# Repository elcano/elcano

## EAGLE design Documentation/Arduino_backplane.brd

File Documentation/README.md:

Elcano Project Documentation
============================

This directory contains all documentation for the Elcnao Project.

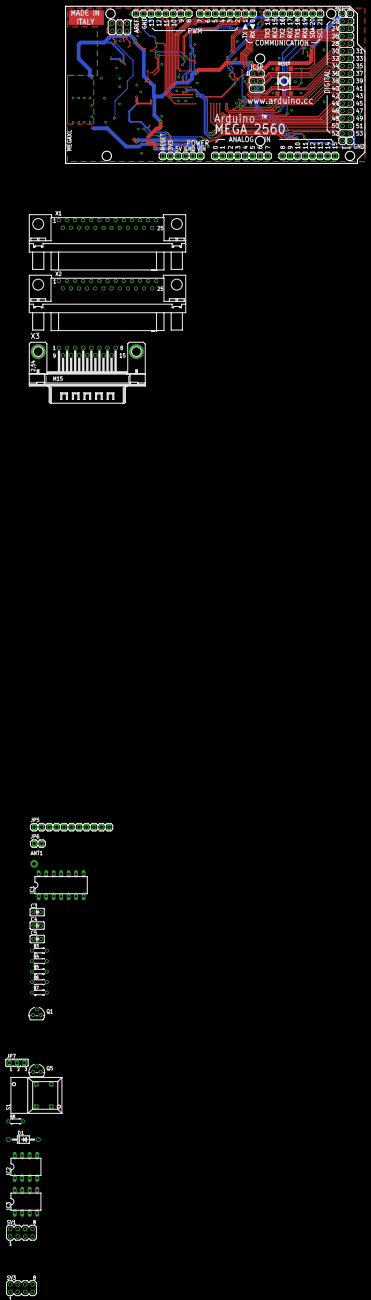
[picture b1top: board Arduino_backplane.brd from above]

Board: 2 copper layers, 101.6 x 53.3 mm, 40 parts (0 on the bottom side), 63 nets.

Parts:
ADCH: 1X08
ADCL: 1X08
ANT1: PAD-01
C3, C5: 0.1uF; C025-025X050
C4: 0.1 uF; C025-025X050
COMMUNICATION: 1X08
D1: 1N4004; DO41-10
IC1: 4013N; DIL14
IC2, IC3: MCP4802; DIL08
ICSP, ICSP1: ICSP; 2X03
JP1, JP2, JP3, JP4: 1X01
JP5: 1X11
JP6: 1X02
JP7: JP2
POWER: 1X06
PWMH: 1X08
PWML: 1X08
Q1, Q5: BF199; TO92
R3, R7: 4.7k; 0204/5
R4: 1M; 0204/5
R5, R6, R8: 10M; 0204/5
RESET: TS42
S1: 5501
SV1: MA04-2
SV3: Steer; MA04-2
X1, X2: M25-HD-20
X3: M15HP
XIOH: 2X08
XIOL: 2X08

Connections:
+5V: C5.1, IC2.1, ICSP.2, ICSP1.2, JP1.1, JP2.1, JP5.3
A1: ADCL.2, SV1.4
A4: ADCL.5, SV3.2
A5: ADCL.6, SV3.4
A10: ADCH.3, X3.2
A11: ADCH.4, X3.1
A13: ADCH.6, X2.6
A14: ADCH.7, X2.7
A15: ADCH.8, X2.8
D6: PWML.7, SV3.8
GND: C3.2, D1.C, IC2.5, IC2.7, IC3.5, IC3.7, ICSP.6, ICSP1.6, JP3.1, JP4.1, JP6.2, POWER.4, POWER.5, PWMH.7, Q1.2, R4.2, RESET.1, RESET.2, S1.NO, X2.24, X3.11
INT0: PWML.3, X3.14
INT2: COMMUNICATION.4, JP5.11
INT3: COMMUNICATION.3, JP5.10
INT4: COMMUNICATION.2, X1.17
INT5: COMMUNICATION.1, X1.16
unnamed: X3.4, XIOH.13
unnamed: PWML.6, X2.16, X3.15
unnamed: IC2.8, X3.12
unnamed: IC2.3, XIOL.2
unnamed: IC2.6, X3.13
unnamed: SV1.6, X2.22
unnamed: ADCL.8, SV3.7
unnamed: C4.1, C4.2, IC1.8, IC1.9, Q5.2, R5.1
unnamed: Q5.3, X3.6
unnamed: X1.25, X3.8
unnamed: Q1.3, X2.25
unnamed: POWER.3, SV3.6, X1.22
unnamed: IC1.11, IC1.13, JP5.6, R3.2
unnamed: ANT1.1, JP6.1
unnamed: JP7.2, R7.2
unnamed: JP5.7, S1.1A, S1.1B
unnamed: IC1.1, JP5.8, JP7.1, JP7.3
unnamed: Q5.1, R3.1
unnamed: IC1.12, R5.2
unnamed: C3.1, IC1.5, R6.1
unnamed: C5.2, IC1.4, IC1.10, R4.1
unnamed: IC1.2, R6.2
unnamed: Q1.1, R7.1
unnamed: D1.A, R8.1
PA0: X1.6, XIOH.16
PA1: X1.5, X2.5, XIOH.15
PA2: X1.7, XIOH.14
PA4: X1.8, XIOH.12
PA5: X1.4, X2.4, XIOH.11
PA6: X1.9, XIOH.10
PA7: X1.3, X2.3, XIOH.9
PB0: IC2.2, XIOL.1
PB2: IC2.4, IC3.4, ICSP.4, XIOL.3
PC0: X1.15, X2.15, XIOH.1
PC1: X1.13, X2.13, XIOH.2
PC2: X1.14, X2.14, XIOH.3
PC3: X1.12, XIOH.4
PC4: X1.1, X2.1, XIOH.5
PC5: X1.11, XIOH.6
PC6: X1.2, X2.2, XIOH.7
PC7: X1.10, XIOH.8
PD7: X1.23, XIOL.16
PL0: IC3.2, XIOL.5
PL3: X1.18, XIOL.8
PL4: SV3.5, XIOL.9
RESET: ICSP.5, POWER.1, RESET.3, RESET.4
RXD3: COMMUNICATION.7, X2.17

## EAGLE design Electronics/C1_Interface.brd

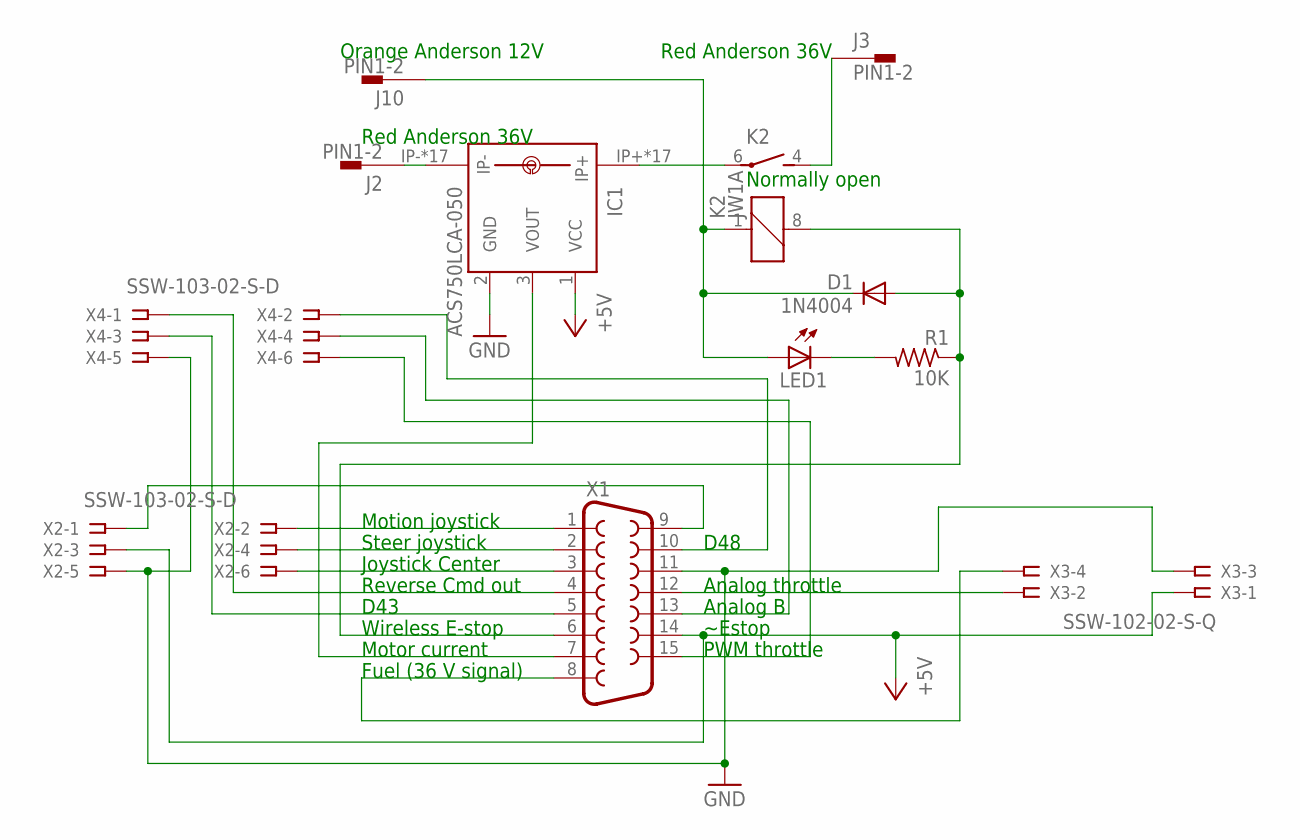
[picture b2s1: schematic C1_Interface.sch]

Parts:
D1: 1N4004; DO41-10
IC1: ACS750LCA-050; ACS75050
J2, J3, J10: PIN1-2; 62221
K2: JW1A
LED1: LED3MM
R1: 10K; 0204/5
X1: F15H
X2, X4: SSW-103-02-S-D
X3: SSW-102-02-S-Q

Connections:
+5V: IC1.1 (VCC), X1.14, X2.3, X3.1
GND: IC1.2 (GND), X1.11, X2.5, X3.3, X4.5
unnamed: D1.C, J10.1, K2.1, LED1.A
unnamed: X1.4, X4.1
unnamed: IC1.3 (VOUT), X1.7
unnamed: LED1.K (C), R1.2
unnamed: X1.8, X3.4
unnamed: J3.1, K2.4 (S)
unnamed: X1.10, X4.2
unnamed: X1.5, X4.3
unnamed: X1.13, X4.4
unnamed: D1.A, K2.8 (2), R1.1, X1.6
unnamed: X1.1, X2.2
unnamed: IC1.IP-, IC1.IP-@2 (IP-), IC1.IP-@3 (IP-), IC1.IP-@4 (IP-), IC1.IP-@5 (IP-), IC1.IP-@6 (IP-), IC1.IP-@7 (IP-), IC1.IP-@8 (IP-), IC1.IP-@9 (IP-), IC1.IP-@10 (IP-), IC1.IP-@11 (IP-), IC1.IP-@12 (IP-), IC1.IP-@13 (IP-), IC1.IP-@14 (IP-), IC1.IP-@15 (IP-), IC1.IP-@16 (IP-), IC1.IP-@17 (IP-), J2.1
unnamed: X1.2, X2.4
unnamed: X1.3, X2.6
unnamed: X1.9, X2.1
unnamed: X1.12, X3.2
unnamed: X1.15, X4.6
unnamed: IC1.IP+, IC1.IP+@2 (IP+), IC1.IP+@3 (IP+), IC1.IP+@4 (IP+), IC1.IP+@5 (IP+), IC1.IP+@6 (IP+), IC1.IP+@7 (IP+), IC1.IP+@8 (IP+), IC1.IP+@9 (IP+), IC1.IP+@10 (IP+), IC1.IP+@11 (IP+), IC1.IP+@12 (IP+), IC1.IP+@13 (IP+), IC1.IP+@14 (IP+), IC1.IP+@15 (IP+), IC1.IP+@16 (IP+), IC1.IP+@17 (IP+), K2.6

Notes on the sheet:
Motion joystick
Steer joystick
Joystick Center
Reverse Cmd out
D43
Wireless E-stop
Motor current
Fuel (36 V signal)
D48
Analog throttle
Analog B
~Estop
PWM throttle
Red Anderson 36V
Normally open
Orange Anderson 12V

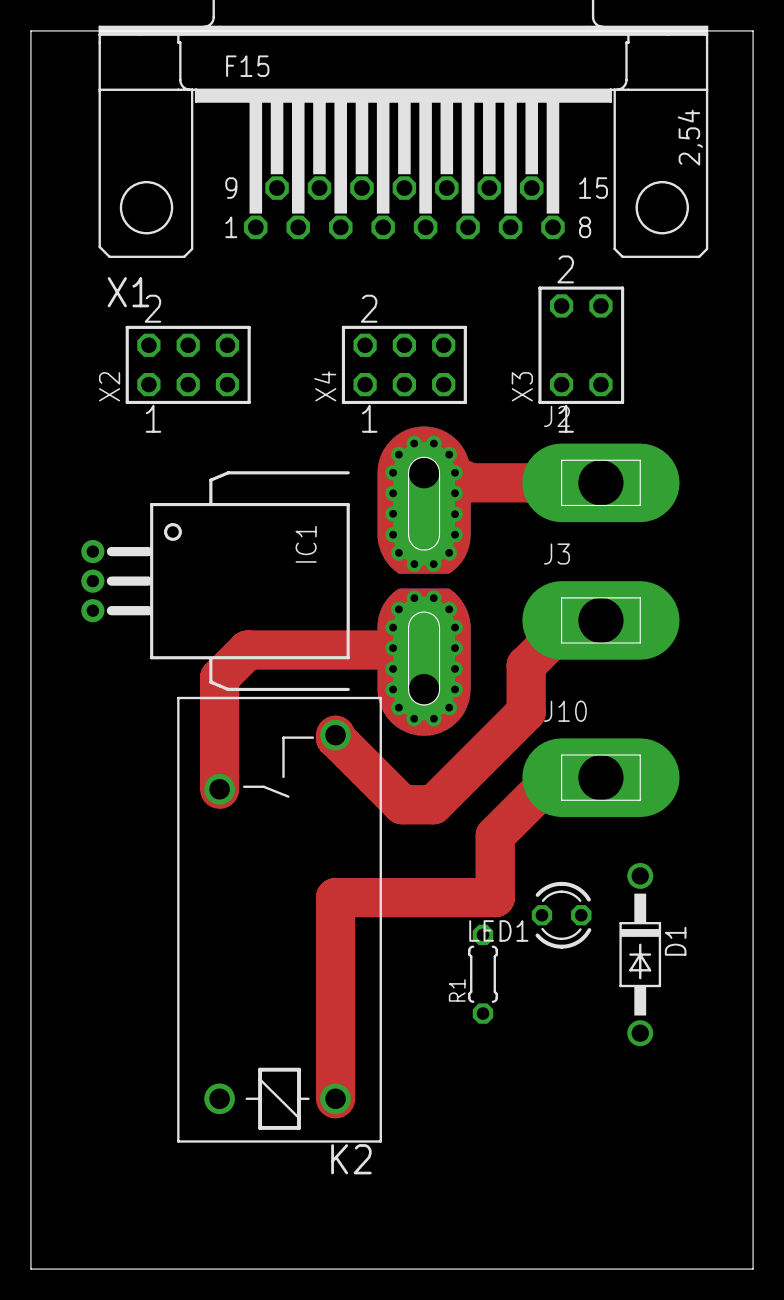
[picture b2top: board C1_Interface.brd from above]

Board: 2 copper layers, 46.7 x 80.0 mm, 12 parts (0 on the bottom side), 20 nets.

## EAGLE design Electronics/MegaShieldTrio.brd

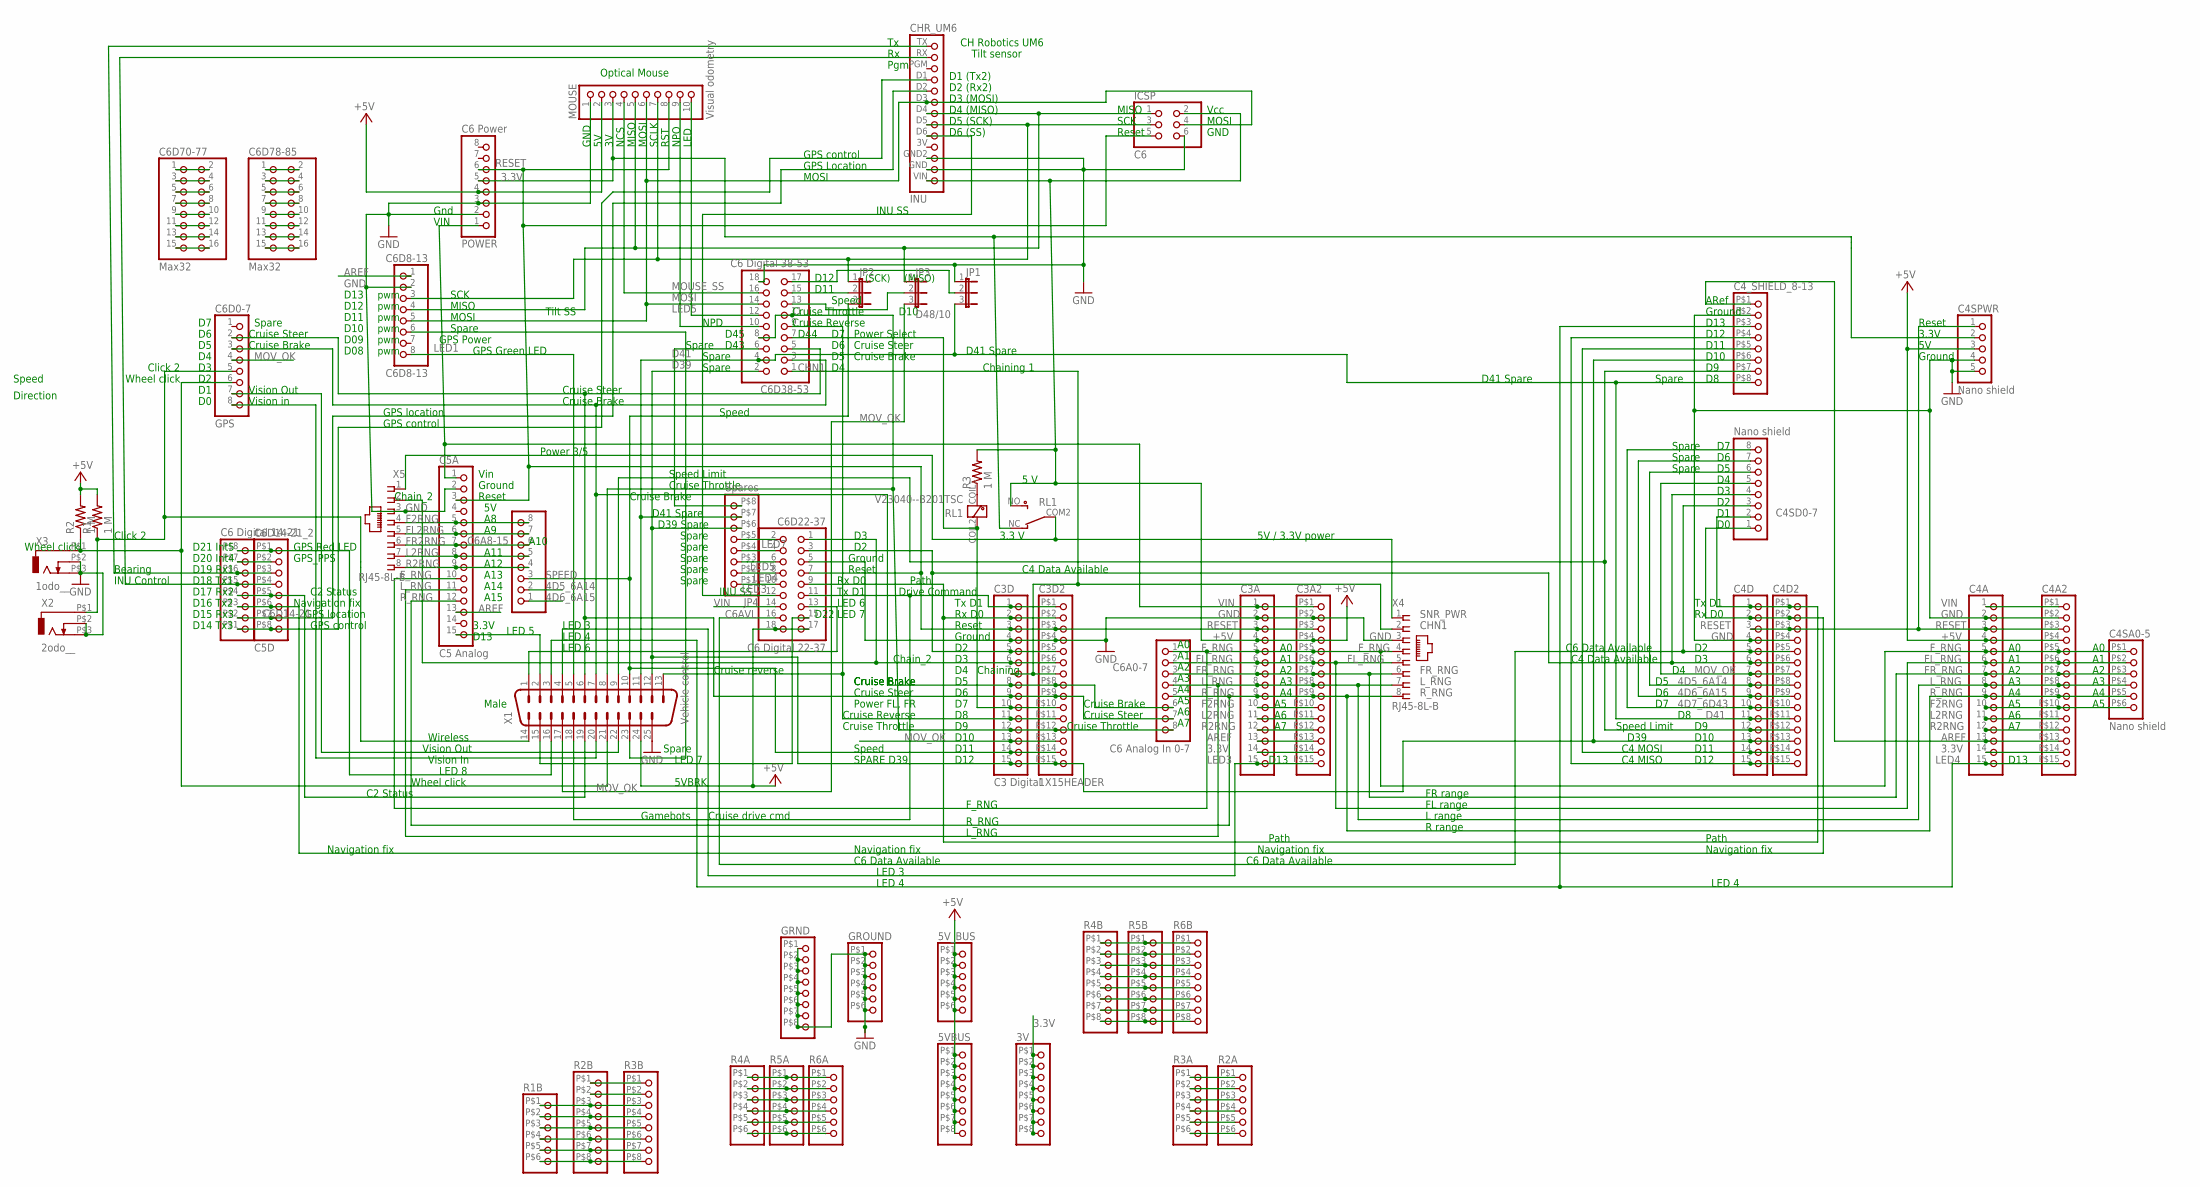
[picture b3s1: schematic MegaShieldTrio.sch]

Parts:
3V: 1X8HEADER
5VBUS: PINHD-1X8SMALL8; 1X8HEADER
5V_BUS: 1X6HEADER
C3A, C4A, C4D: 1X15
C3A2, C4A2, C4D2: 1X15HEADER
C3D: C3 Digital; 1X15
C3D2: 1X15HEADER
C4SA0-5: Nano shield; 1X6HEADER
C4SD0-7: Nano shield; 1X08
C4SPWR: Nano shield; 1X05
C4_SHIELD_8-13: 1X8HEADER
C5A: C5 Analog; 1X15
C6A0-7: C6 Analog In 0-7; 1X08
C6A8-15: 1X08
C6D0-7: GPS; 1X08
C6D8-13: C6D8-13; 1X08
C6D14-21: C6 Digital 14-21; 1X8HEADER
C6D14-21_2: C5D; 1X8HEADER
C6D22-37: C6 Digital 22-37; 2X09
C6D38-53: C6 Digital 38-53; 2X09
C6D70-77, C6D78-85: Max32; 2X08
GRND: PINHD-1X8SMALL8; 1X8HEADER
GROUND: 1X6HEADER
ICSP: C6; 2X03
INU: CHR_UM6
JP1, JP2: JP2
JP3: D48/10; JP2
JP4: Spares; 1X8HEADER
MOUSE: Visual odometry; 1X10
POWER: C6 Power; 1X08
R1, R2, R3: 1 M; 0207/10
R1B, R2A, R3A, R4A, R5A: 1X6HEADER
R2B, R3B, R4B, R5B, R6B: PINHD-1X8SMALL8; 1X8HEADER
R6A: 1X6HEADER
RL1: V23040--B201TSC; TSC-112L3H
X1: Vehicle control; M25H
X2: 2odo__; ODO_JACK
X3: 1odo__; ODO_JACK
X4, X5: RJ45-8L-B; RJ45-NO-SHIELD

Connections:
3.3V: 3V.P$1 (1), 3V.P$2 (2), 3V.P$3 (3), 3V.P$4 (4), 3V.P$5 (5), 3V.P$6 (6), 3V.P$7 (7), 3V.P$8 (8), C3A.14, C3A2.P$14 (14), C4A.14, C4A2.P$14 (14), C4SPWR.2, MOUSE.3, POWER.5, RL1.NC (4)
4D5_6A14: C4D.8, C4D2.P$8 (8), C4SD0-7.6, C6A8-15.2
4D6_6A15: C4D.9, C4D2.P$9 (9), C4SD0-7.7, C6A8-15.1
4D7_6D43: C4D.10, C4D2.P$10 (10), C4SD0-7.8
6D10_2A6: C6D8-13.6, X1.23
+5V: 5VBUS.P$1 (1), 5VBUS.P$2 (2), 5VBUS.P$3 (3), 5VBUS.P$4 (4), 5VBUS.P$5 (5), 5VBUS.P$6 (6), 5VBUS.P$7 (7), 5VBUS.P$8 (8), 5V_BUS.P$1 (1), 5V_BUS.P$2 (2), 5V_BUS.P$3 (3), 5V_BUS.P$4 (4), 5V_BUS.P$5 (5), 5V_BUS.P$6 (6), C3A.4, C3A2.P$4 (4), C4A.4, C4A2.P$4 (4), C4SPWR.3, C6D22-37.17, C6D22-37.18, ICSP.2, INU.VIN (1), MOUSE.2, POWER.4, R1.2, R2.2, R3.2, RL1.NO (6), X1.24
AREF: C3A.13, C3A2.P$13 (13), C4A.13, C4A2.P$13 (13), C4_SHIELD_8-13.P$1 (1), C5A.13, C6D8-13.1
C2STAT: C6D14-21.P$4 (4), C6D14-21_2.P$5 (5), X1.19
C4AVL: C3D.5, C3D2.P$5 (5), C4D.6, C4D2.P$6 (6), C4SD0-7.4, C6D22-37.3
C4D11: C4D.14, C4D2.P$14 (14), C4_SHIELD_8-13.P$5 (5)
C4D12: C4D.15, C4D2.P$15 (15), C4_SHIELD_8-13.P$4 (4)
C6AVL: C4D.5, C4D2.P$5 (5), C4SD0-7.3, C6D22-37.16
C6D29: C6D22-37.10, JP4.P$1 (1)
C6D31: C6D22-37.8, JP4.P$2 (2)
C6D33: C6D22-37.6, JP4.P$3 (3)
C6D35: C6D22-37.4, JP4.P$4 (4)
C6D37: C6D22-37.2, JP4.P$5 (5)
CHN1: C3D.7, C3D2.P$7 (7), C6D38-53.1, X4.2
CHN2: C3D.6, C3D2.P$6 (6), C6D22-37.1, X5.2
CLICK1: C6D0-7.6, R2.1, X1.21, X3.P$1 (1)
CLICK2: C6D0-7.5, R1.1, X1.14, X2.P$1 (1)
CRS_BRK: C3D.8, C3D2.P$8 (8), C6A0-7.6, C6D0-7.3, C6D38-53.3, X1.7
CRS_REV: C3D.11, C3D2.P$11 (11), C6D38-53.9, X1.13
CRS_STR: C3D.9, C3D2.P$9 (9), C6A0-7.7, C6D0-7.2, C6D38-53.5, X1.6
CRS_THR: C3D.12, C3D2.P$12 (12), C6A0-7.8, C6D38-53.8, C6D38-53.11, X1.8
D39: C3D.15, C3D2.P$15 (15), C4D.13, C4D2.P$13 (13), C4_SHIELD_8-13.P$6 (6), C6D38-53.2, JP4.P$6 (6), X1.12
D41: C4D.11, C4D2.P$11 (11), C4_SHIELD_8-13.P$8 (8), C6D38-53.4, JP1.3, JP4.P$7 (7), X1.11
DRV_CMD: C3D.1, C3D2.P$1 (1), C6D22-37.11, X1.18
F2RNG: C3A.10, C3A2.P$10 (10), C4A.10, C4A2.P$10 (10), C4SA0-5.P$6 (6), C5A.5, C6A8-15.8, X5.4
FL2RNG: C5A.6, C6A8-15.7, X5.5
FL_RNG: C3A.6, C3A2.P$6 (6), C4A.6, C4A2.P$6 (6), C4SA0-5.P$2 (2), C6A0-7.2, X4.5
FR2RNG: C5A.7, C6A8-15.6, X5.6
FR_RNG: C3A.7, C3A2.P$7 (7), C4A.7, C4A2.P$7 (7), C4SA0-5.P$3 (3), C6A0-7.3, X4.6
F_RNG: C3A.5, C3A2.P$5 (5), C4A.5, C4A2.P$5 (5), C4SA0-5.P$1 (1), C5A.10, C6A0-7.1, X4.4
GND: C3A.2, C3A2.P$2 (2), C3D.4, C3D2.P$4 (4), C4A.2, C4A2.P$2 (2), C4D.4, C4D2.P$4 (4), C4SPWR.4, C4SPWR.5, C4_SHIELD_8-13.P$2 (2), C5A.2, C6D8-13.2, C6D22-37.5, C6D38-53.18, GRND.P$1 (1), GRND.P$2 (2), GRND.P$3 (3), GRND.P$4 (4), GRND.P$5 (5), GRND.P$6 (6), GRND.P$7 (7), GRND.P$8 (8), GROUND.P$1 (1), GROUND.P$2 (2), GROUND.P$3 (3), GROUND.P$4 (4), GROUND.P$5 (5), GROUND.P$6 (6), ICSP.6, INU.GND (2), INU.GND2 (3), JP1.1, MOUSE.1, POWER.2, POWER.3, X1.25, X2.P$2 (2), X2.P$3 (3), X3.P$2 (2), X3.P$3 (3), X4.3, X5.3
GPS_CNTRL: C6D14-21.P$1 (1), C6D14-21_2.P$8 (8), INU.D1 (10)
GPS_LOC: C6D14-21.P$2 (2), C6D14-21_2.P$7 (7), INU.D2 (9)
INU_BRN: C6D14-21.P$6 (6), C6D14-21_2.P$3 (3), INU.TX (13)
INU_CNTRL: C6D14-21.P$5 (5), C6D14-21_2.P$4 (4), INU.RX (12)
INU_SS: C6D22-37.12, INU.D6 (5)
L2RNG: C3A.11, C3A2.P$11 (11), C4A.11, C4A2.P$11 (11), C5A.8, C6A8-15.5, X5.7
LED1: C6D8-13.8, X1.5
LED3: C3A.15, C3A2.P$15 (15), X1.4
LED4: C4A.15, C4A2.P$15 (15), C4_SHIELD_8-13.P$3 (3), X1.3
LED5: C5A.15, C6D38-53.12, MOUSE.10, X1.2
LED6: C6D22-37.13, X1.1
LED7: C6D22-37.15, X1.15
LED8: C6D14-21.P$8 (8), C6D14-21_2.P$1 (1), X1.16
L_RNG: C3A.8, C3A2.P$8 (8), C4A.8, C4A2.P$8 (8), C4SA0-5.P$4 (4), C5A.11, C6A0-7.4, X4.7
MISO: C6D8-13.4, ICSP.1, INU.D4 (7), JP3.1, MOUSE.5
MOSI: C6D8-13.5, C6D38-53.14, ICSP.4, INU.D3 (8), MOUSE.6
MOUSE_SS: C6D38-53.16, MOUSE.4
MOV_OK: C3D.13, C3D2.P$13 (13), C4D.7, C4D2.P$7 (7), C4SD0-7.5, C6D0-7.4, JP3.3, X1.17
unnamed: R2B.P$1 (1), R3B.P$1 (1)
unnamed: R2B.P$2 (2), R3B.P$2 (2)
unnamed: C6D38-53.6, JP4.P$8 (8)
unnamed: C6D38-53.15, JP2.2
unnamed: C6D38-53.13, JP3.2
unnamed: C6D38-53.17, JP1.2
unnamed: C6D14-21.P$7 (7), C6D14-21_2.P$2 (2)
unnamed: R3.1, RL1.COIL1 (1)
unnamed: R1B.P$1 (1), R2B.P$3 (3), R3B.P$3 (3)
unnamed: R1B.P$2 (2), R2B.P$4 (4), R3B.P$4 (4)
unnamed: R1B.P$3 (3), R2B.P$5 (5), R3B.P$5 (5)
unnamed: R1B.P$4 (4), R2B.P$6 (6), R3B.P$6 (6)
unnamed: R1B.P$5 (5), R2B.P$7 (7), R3B.P$7 (7)
unnamed: R1B.P$6 (6), R2B.P$8 (8), R3B.P$8 (8)
unnamed: R4A.P$1 (1), R5A.P$1 (1), R6A.P$1 (1)
unnamed: R4A.P$2 (2), R5A.P$2 (2), R6A.P$2 (2)
unnamed: R4A.P$3 (3), R5A.P$3 (3), R6A.P$3 (3)
unnamed: R4A.P$4 (4), R5A.P$4 (4), R6A.P$4 (4)
unnamed: R4A.P$5 (5), R5A.P$5 (5), R6A.P$5 (5)
unnamed: R4A.P$6 (6), R5A.P$6 (6), R6A.P$6 (6)
unnamed: R4B.P$1 (1), R5B.P$1 (1), R6B.P$1 (1)
unnamed: C6D78-85.1, C6D78-85.2
unnamed: C6D78-85.3, C6D78-85.4
unnamed: R4B.P$2 (2), R5B.P$2 (2), R6B.P$2 (2)
unnamed: R4B.P$3 (3), R5B.P$3 (3), R6B.P$3 (3)
unnamed: C6D78-85.5, C6D78-85.6
unnamed: R4B.P$5 (5), R5B.P$5 (5), R6B.P$5 (5)
unnamed: C6D78-85.7, C6D78-85.8
unnamed: C6D78-85.9, C6D78-85.10
unnamed: R4B.P$6 (6), R5B.P$6 (6), R6B.P$6 (6)
unnamed: R4B.P$7 (7), R5B.P$7 (7), R6B.P$7 (7)
unnamed: R4B.P$8 (8), R5B.P$8 (8), R6B.P$8 (8)
unnamed: R2A.P$1 (1), R3A.P$1 (1)
unnamed: R2A.P$2 (2), R3A.P$2 (2)
unnamed: C6D78-85.11, C6D78-85.12
unnamed: C6D78-85.13, C6D78-85.14
unnamed: C6D78-85.15, C6D78-85.16
unnamed: R2A.P$3 (3), R3A.P$3 (3)
unnamed: C6D70-77.1, C6D70-77.2
unnamed: R2A.P$4 (4), R3A.P$4 (4)
unnamed: R2A.P$5 (5), R3A.P$5 (5)
unnamed: C6D70-77.3, C6D70-77.4
unnamed: C6D70-77.5, C6D70-77.6
unnamed: C6D70-77.7, C6D70-77.8
unnamed: C6D70-77.9, C6D70-77.10
unnamed: C6D70-77.11, C6D70-77.12
unnamed: C6D70-77.13, C6D70-77.14
unnamed: C6D70-77.15, C6D70-77.16
unnamed: R2A.P$6 (6), R3A.P$6 (6)
NAV_FIX: C4D.2, C4D2.P$2 (2), C4SD0-7.1, C6D14-21.P$3 (3), C6D14-21_2.P$6 (6)
NPD: C6D38-53.10, MOUSE.9
PATH: C3D.2, C3D2.P$2 (2), C4D.1, C4D2.P$1 (1), C4SD0-7.2, C6D22-37.9
PWR_SEL: C3D.10, C3D2.P$10 (10), C6D38-53.7, RL1.COIL2 (2)
R2RNG: C3A.12, C3A2.P$12 (12), C4A.12, C4A2.P$12 (12), C5A.9, C6A8-15.4, X5.8
R5B: R4B.P$4 (4), R5B.P$4 (4), R6B.P$4 (4)
RESET: C3A.3, C3A2.P$3 (3), C3D.3, C3D2.P$3 (3), C4A.3, C4A2.P$3 (3), C4D.3, C4D2.P$3 (3), C4SPWR.1, C5A.3, C6D22-37.7, ICSP.5, MOUSE.8, POWER.6
R_RNG: C3A.9, C3A2.P$9 (9), C4A.9, C4A2.P$9 (9), C4SA0-5.P$5 (5), C5A.12, C6A0-7.5, X4.8
SCK: C6D8-13.3, ICSP.3, INU.D5 (6), JP2.1, MOUSE.7
SNR_PWR: RL1.COM2 (5), X4.1, X5.1
SPD_LMT: C4D.12, C4D2.P$12 (12), C4_SHIELD_8-13.P$7 (7), X1.9
SPEED: C3D.14, C3D2.P$14 (14), C6A8-15.3, JP2.3, X1.10
VIN: C3A.1, C3A2.P$1 (1), C4A.1, C4A2.P$1 (1), C5A.1, C6D22-37.14, POWER.1
VIS_IN: C6D0-7.8, X1.20
VIS_OUT: C6D0-7.7, X1.22

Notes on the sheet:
pwm
(SCK)
(MISO)
Cruise Brake
Cruise Throttle
Cruise Steer
Gnd
Male
A10
A11
A13
A14
A15
5VBRK
D45
D43
D10
D11
D12
D13
D09
D08
VIN
Rx D0
Tx D1
Reset
Ground
3.3V
ARef
Path
Navigation fix
D14 Tx3
D15 Rx3
D16 Tx2
D17 Rx2
D18 Tx1
D19 Rx1
D20 Int4
D21 Int5
C6 Data Available

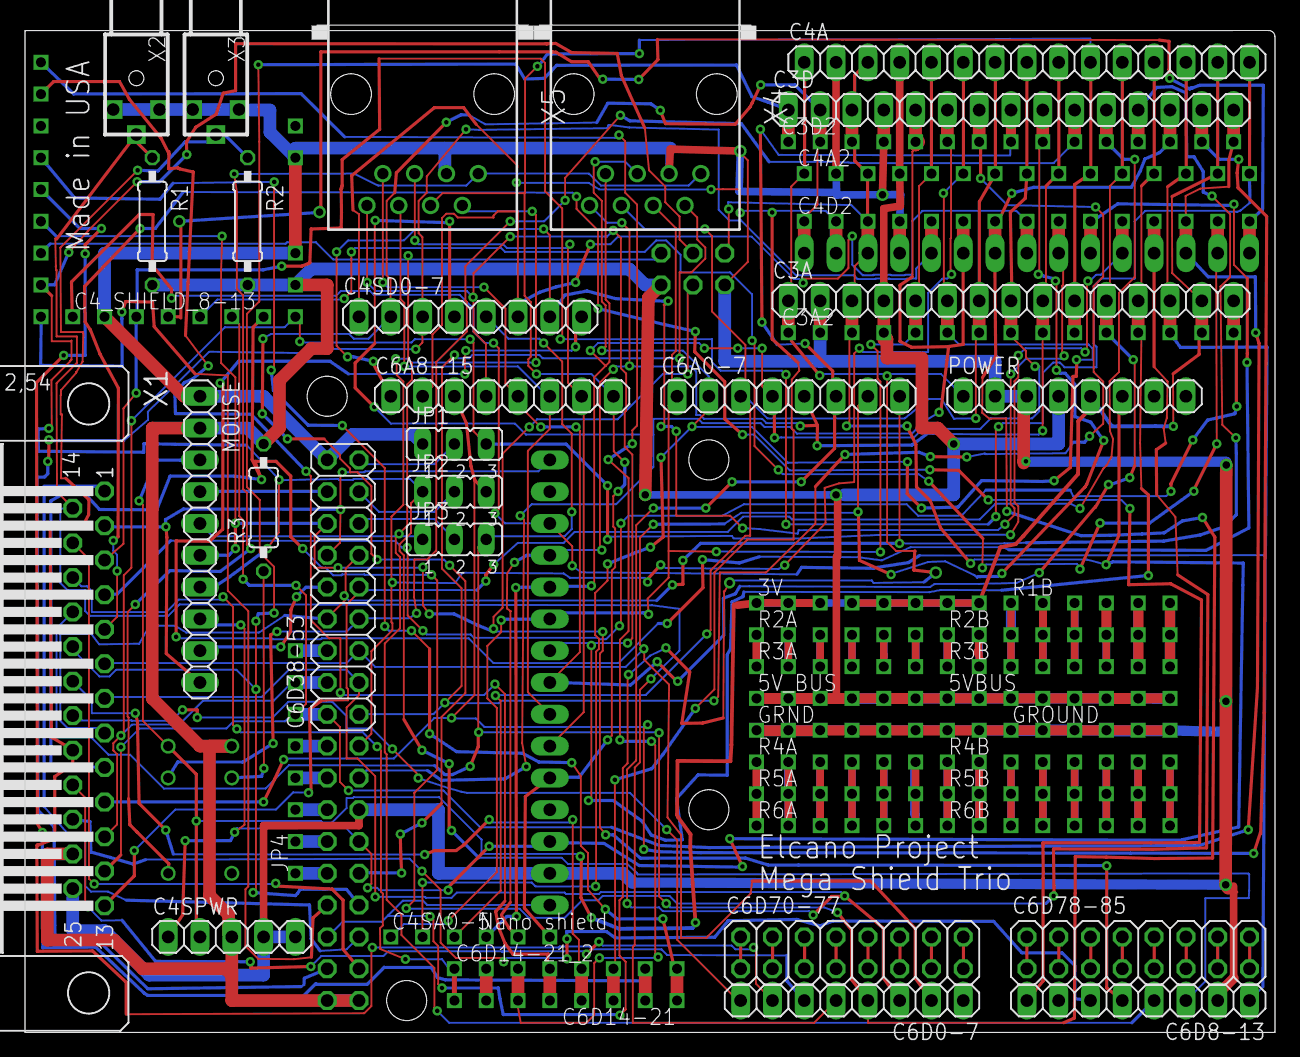
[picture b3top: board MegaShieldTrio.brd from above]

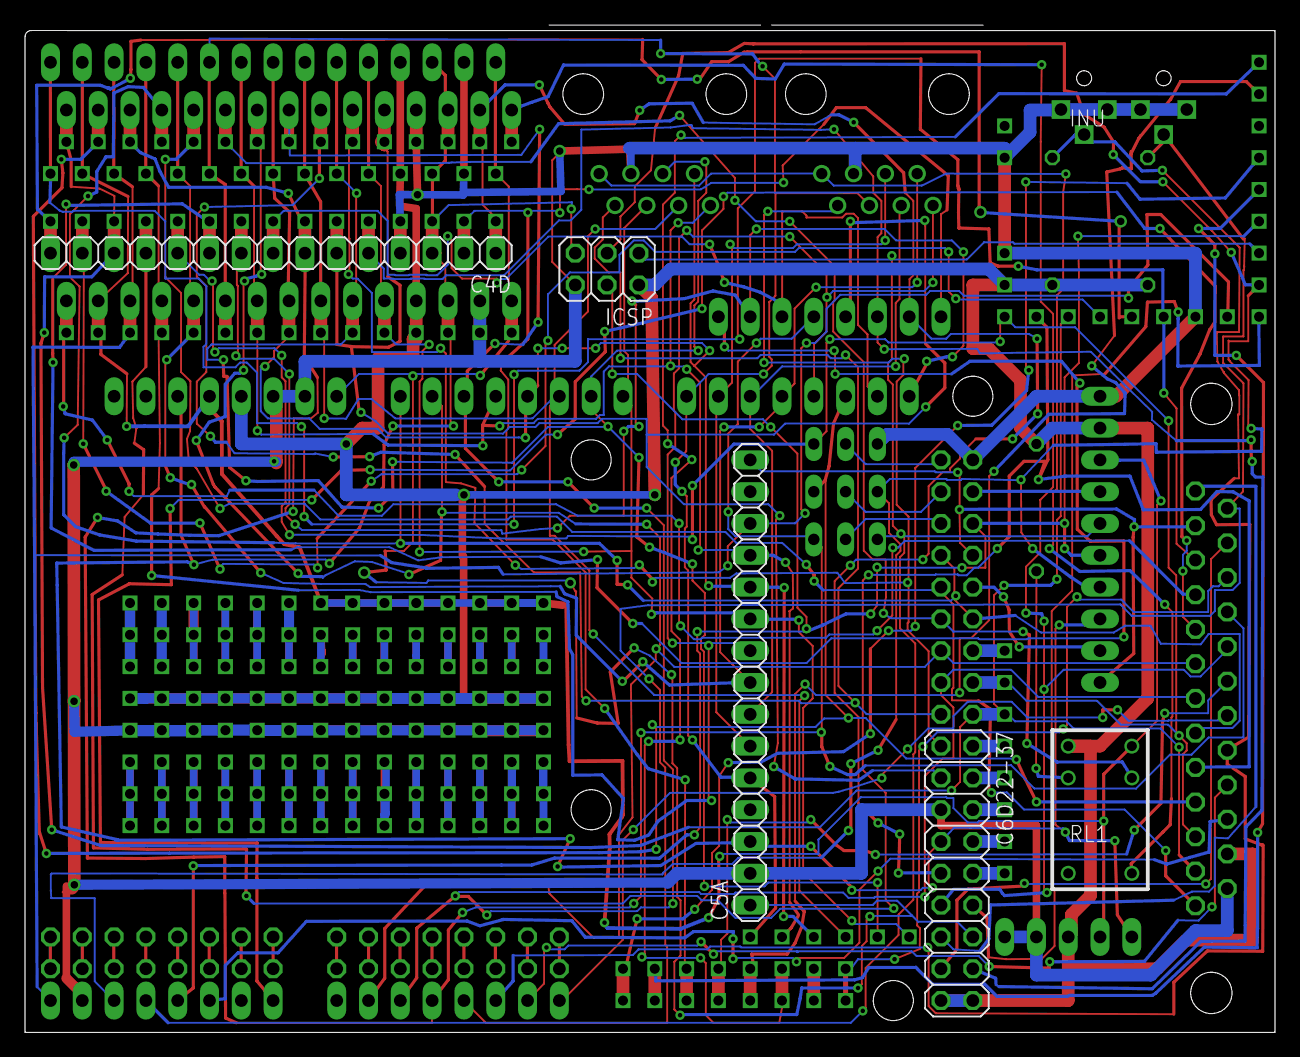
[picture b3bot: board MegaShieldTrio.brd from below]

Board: 2 copper layers, 99.8 x 80.0 mm, 56 parts (6 on the bottom side), 117 nets.

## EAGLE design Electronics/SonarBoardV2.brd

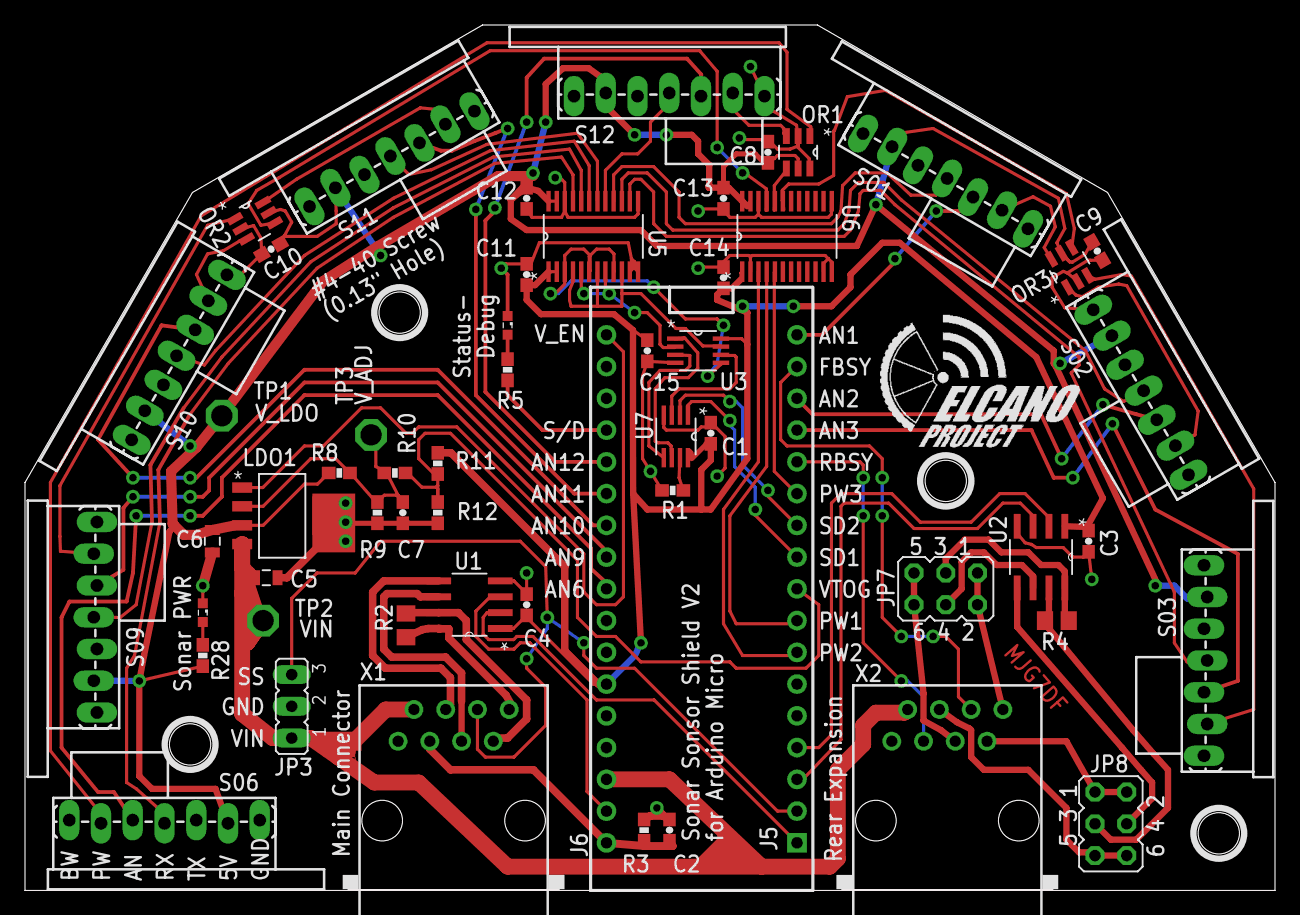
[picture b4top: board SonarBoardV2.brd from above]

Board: 2 copper layers, 100.0 x 69.2 mm, 60 parts (0 on the bottom side), 69 nets.

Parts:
C1, C3, C4, C8, C9, C10, C11, C12, C13, C14, C15: 0.1uF; 0603-CAP
C2, C7: DNS; 0603-CAP
C5, C6: 10uF, 25V; 0805
J5: HEAD17-NOSS
J6: HEAD17-NOSS-1
JP3: JP2
JP7, JP8: JP3Q
LDO1: LP38693MP-ADJ; SOT150P696X180-5N
LED1, LED2: SML0603
OR1, OR2, OR3: SN74LVC1G332DBVR; SOT95P280X145-6N
R1: 0; 0603-RES
R2, R4: 100; R0805
R3, R11, R12: DNS; 0603-RES
R5, R28: 600; 0603-RES
R8: 33k; 0603-RES
R9: 12k; 0603-RES
R10: 100k; 0603-RES
S01, S02, S03, S06, S09, S10, S11, S12: MaxSonar; XL-MAXSONAR-PACKAGE
TP1, TP2, TP3: TPPAD1-17; P1-17
U1, U2: DS8921M; SOIC127O620X175-8N
U3: SN74LVC3G14DCTR; SOP65P400X130-8N
U5, U6: SN74LVCH8T245PWR; SOP65P640X120-24N
U7: SN74LVC1G139DCTR; SOP65P400X130-8N@1
U$15, U$16, U$17, U$18: STAND-OFF
X1, X2: RJ45-8L-B; RJ45-NO-SHIELD

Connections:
+5V: C1.1, C3.1, C4.1, C11.1, C14.1, C15.1, J6.6, R11.2, U1.1, U2.1, U3.8, U5.1, U5.2, U6.1, U7.8
A0: J6.14, R5.1
AN1: J5.17, S01.3
AN2: J5.15, S02.3
AN3: J5.14, S03.3
AN6: J6.9, S06.3
AN9: J6.10, S09.3
AN10: J6.11, S10.3
AN11: J6.12, S11.3
AN12: J6.13, S12.3
F_BSY: J5.16, X2.6
G01: U3.7, U5.4, U5.7, U5.10
G10: U3.5, U5.3, U5.6, U5.9
G11: U3.2, U5.5, U5.8
GND: C1.2, C2.2, C3.2, C4.2, C5.2, C6.2, C7.2, C8.2, C9.2, C10.2, C11.2, C12.2, C13.2, C14.2, C15.2, J5.6, J6.4, JP3.2, LDO1.5, LED1.C, LED2.C, OR1.2, OR1.6, OR2.2, OR3.2, R1.2, R3.1, R9.1, R12.1, S01.1, S01.7, S02.1, S02.7, S03.1, S03.7, S06.1, S06.7, S09.1, S09.7, S10.1, S10.7, S11.1, S11.7, S12.1, S12.7, U1.4, U2.4, U3.4, U5.11, U5.12, U5.13, U5.22, U6.2, U6.11, U6.12, U6.13, U6.22, U7.4, X1.1, X2.1
MISO: J6.2, U1.3
MISO+: U1.6, X1.5
MISO-: U1.5, X1.4
MOSI: J5.1, U1.2
MOSI+: R2.1, U1.8, X1.8
MOSI-: R2.2, U1.7, X1.7
MRX+_STX+: JP7.1, JP7.2, X2.8
MRX-_STX-: JP8.1, JP8.2, X2.7
MTX+_SRX+: JP7.5, JP7.6, X2.5
MTX-_SRX-: JP8.5, JP8.6, X2.4
unnamed: LED2.A, R5.2
unnamed: LED1.A, R28.2
unnamed: U3.1, U7.6
unnamed: U3.3, U7.5
unnamed: U3.6, U7.3
unnamed: R1.1, U7.7
unnamed: OR1.4, U6.20
unnamed: OR2.4, U6.21
unnamed: OR3.4, U6.19
PW1: OR3.6, S01.2
PW2: OR3.1, S02.2
PW3: OR3.3, S03.2
PW6: OR1.1, S06.2
PW9: OR2.1, S09.2
PW10: OR2.3, S10.2
PW11: OR2.6, S11.2
PW12: OR1.3, S12.2
PW_OR1: J5.8, U6.4
PW_OR2: J5.7, U6.3
PW_OR3: J5.12, U6.5
RX: J5.4, U2.2
RX1: S01.4, U5.16
RX2: S02.4, U5.15
RX3: S03.4, U5.14
RX6: S06.4, U5.21
RX9: S09.4, U5.20
RX10: S10.4, U5.19
RX11: S11.4, U5.18
RX12: S12.4, U5.17
RX+: JP7.3, R4.1, U2.8
RX-: JP8.3, R4.2, U2.7
R_BSY: J5.13, X2.3
SCK: C2.1, J6.1, R3.2, X1.3
SS: J5.2, JP3.3, X1.6
S_DEC_1: J5.10, U7.1
S_DEC_2: J5.11, U7.2
TX: J5.3, U2.3
TX+: JP7.4, U2.6
TX-: JP8.4, U2.5
VIN: C5.1, J6.3, JP3.1, LDO1.4, TP2.TP, X1.2, X2.2
V_ADJ: C7.1, LDO1.2, R8.1, R9.2, R10.2, TP3.TP
V_EN: J6.17, LDO1.1
V_LDO: C6.1, C8.1, C9.1, C10.1, C12.1, C13.1, LDO1.3, OR1.5, OR2.5, OR3.5, R8.2, R28.1, S01.6, S02.6, S03.6, S06.6, S09.6, S10.6, S11.6, S12.6, TP1.TP, U5.23, U5.24, U6.23, U6.24
V_TOGGLE: J5.9, R10.1, R11.1, R12.2

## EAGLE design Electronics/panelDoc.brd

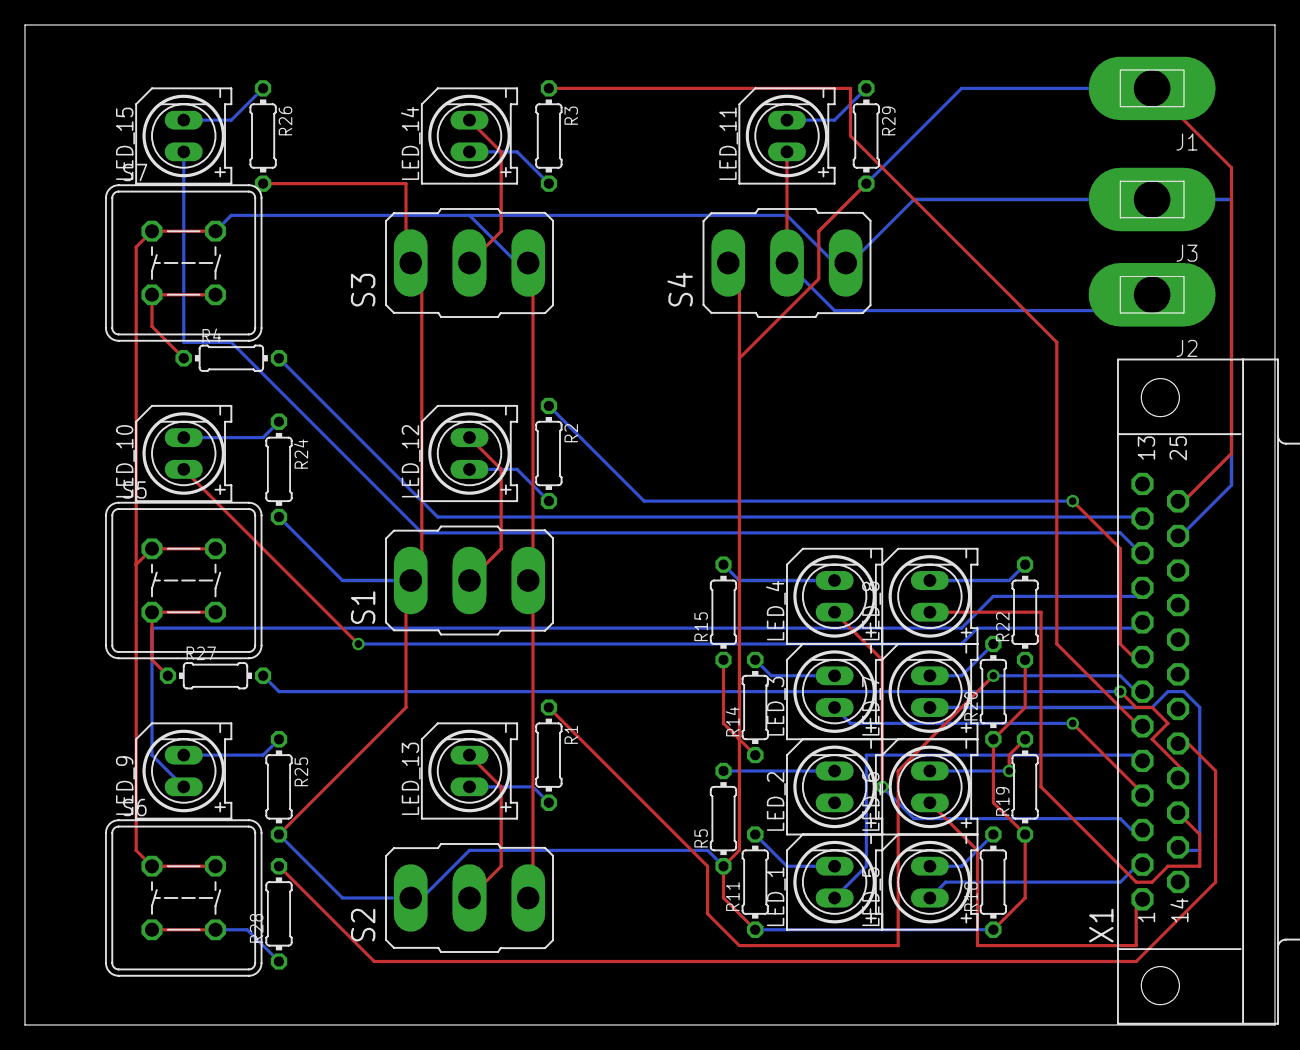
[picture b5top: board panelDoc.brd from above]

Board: 2 copper layers, 100.0 x 80.0 mm, 44 parts (0 on the bottom side), 40 nets.

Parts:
J1, J2, J3: PIN1-2; 62221
LED_1, LED_2, LED_3, LED_4, LED_5, LED_6, LED_7, LED_8: Q62902-B156
LED_9: Stop LED; Q62902-B156
LED_10: Cruise LED; Q62902-B156
LED_11: On LED; Q62902-B156
LED_12: Motor LED; Q62902-B156
LED_13: Brake LED; Q62902-B156
LED_14: Steer LED; Q62902-B156
LED_15: Reverse LED; Q62902-B156
R1, R2, R3: 200; 0204/7
R4, R27, R28: 220; 0204/7
R5, R11, R14, R15, R18, R19, R20, R22, R24, R25, R26: 1K; 0204/7
R29: 10K; 0204/7
S1: Motor; M9040P
S2: Brake; M9040P
S3: Steer; M9040P
S4: On; M9040P
S5: Cruise Switch; DTE6K
S6: Stop switch; DTE6K
S7: Reverse Switch; DTE6K
X1: 182-025-MALE

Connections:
+5V: J3.1, S1.3, S2.3, S3.3, S4.3, S5.1, S5.2, S6.1, S6.2, S7.1, S7.2, X1.24
GND: J1.1, R5.1, R11.1, R14.1, R15.1, R18.1, R19.1, R20.1, R22.1, R24.2, R25.2, R26.2, R29.2, S1.1, S2.1, S3.1, S4.1, X1.25
unnamed: R3.1, X1.6
unnamed: LED_8.K, R22.2
unnamed: LED_10.K, R24.1
unnamed: LED_3.K, R14.2
unnamed: LED_3.A, X1.4
unnamed: LED_4.K, R15.2
unnamed: LED_4.A, X1.3
unnamed: LED_1.A, X1.5
unnamed: LED_8.A, X1.16
unnamed: LED_5.K, R18.2
unnamed: LED_5.A, X1.2
unnamed: LED_6.K, R19.2
unnamed: LED_6.A, X1.1
unnamed: LED_7.K, R20.2
unnamed: LED_10.A, X1.9
unnamed: LED_1.K, R11.2
unnamed: J2.1, LED_11.A, S4.2
unnamed: LED_11.K, R29.1
unnamed: R27.2, X1.17
unnamed: LED_7.A, X1.15
unnamed: LED_12.A, R2.2
unnamed: LED_15.A, X1.11
unnamed: LED_12.K, S1.2
unnamed: LED_13.K, S2.2
unnamed: LED_9.K, R25.1
unnamed: LED_9.A, X1.10
unnamed: LED_14.A, R3.2
unnamed: R2.1, X1.8
unnamed: LED_13.A, R1.2
unnamed: LED_14.K, S3.2
unnamed: R4.2, X1.12
unnamed: R1.1, X1.7
unnamed: R4.1, S7.3, S7.4
unnamed: R27.1, S5.3, S5.4
unnamed: R28.2, X1.18
unnamed: R28.1, S6.3, S6.4
unnamed: LED_2.K, R5.2
REVERSE: LED_15.K, R26.1

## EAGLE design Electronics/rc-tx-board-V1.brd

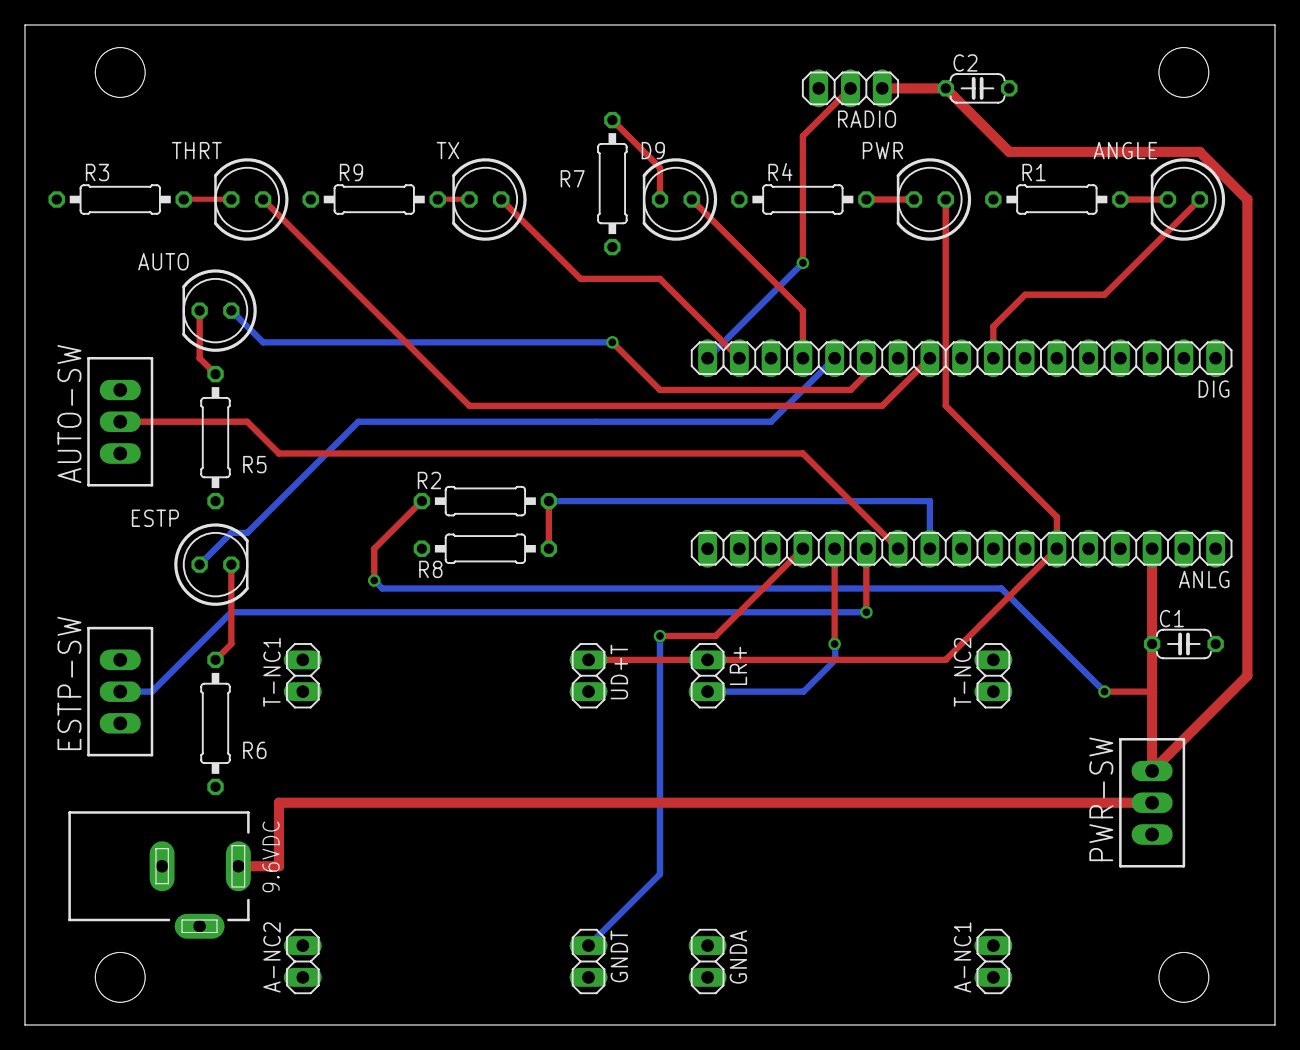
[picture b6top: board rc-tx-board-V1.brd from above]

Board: 2 copper layers, 100.0 x 80.0 mm, 33 parts (0 on the bottom side), 23 nets.

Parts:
9.6VDC: DCJ0202
A-NC1, A-NC2: 1X02
ANGLE: LED5MM
ANLG: 1X17
AUTO: LED5MM
AUTO-SW: TL36PO; TL3XPO
C1, C2: 100nF; C050-024X044
D9: LED5MM
DIG: 1X17
ESTP: LED5MM
ESTP-SW: TL36PO; TL3XPO
GNDA: 1X02
GNDT: 1X02
LR+: 1X02
PWR: LED5MM
PWR-SW: TL36PO; TL3XPO
R1, R3, R4, R5, R6, R7, R9: 1k; 0207/10
R2: 22k; 0207/10
R8: 10k; 0207/10
RADIO: 1X03
T-NC1, T-NC2: 1X02
THRT: LED5MM
TX: LED5MM
UD+T: 1X02

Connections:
5V: ANLG.6, LR+.1, PWR.A, UD+T.1
9.6V: ANLG.3, C1.1, C2.1, PWR-SW.3, R2.2, RADIO.1
9.6V_SOURCE: 9.6VDC.1, PWR-SW.2
ANGLE: ANGLE.A, DIG.8
ANGLE_R: ANGLE.K, R1.2
ANGLE_SENS: ANLG.13, LR+.2
AUTO: AUTO.A, DIG.12
AUTO_R: AUTO.K, R5.2
AUTO_SW: ANLG.11, AUTO-SW.2
BAT_HEALTH: ANLG.10, R2.1, R8.2
ESTP: DIG.13, ESTP.A
ESTP_R: ESTP.K, R6.2
ESTP_SW: ANLG.12, ESTP-SW.2
GND: 9.6VDC.3, ANLG.5, AUTO-SW.3, C1.2, C2.2, DIG.6, ESTP-SW.3, GNDA.2, GNDT.2, R1.1, R3.1, R4.1, R5.1, R6.1, R7.1, R8.1, R9.1, RADIO.3
PWR_R: PWR.K, R4.2
RADIO_SIG: DIG.17, RADIO.2
SPARE: D9.A, DIG.14
SPARE_R: D9.K, R7.2
THROTTLE_SENS: ANLG.14, GNDT.1
THRT: DIG.10, THRT.A
THRT_R: R3.2, THRT.K
TX: DIG.16, TX.A
TX_R: R9.2, TX.K

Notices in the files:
parts and their libraries:
SparkFun-Passives: Licensing: Creative Commons ShareAlike 4.0 International - https://creativecommons.org/licenses/by-sa/4.0
